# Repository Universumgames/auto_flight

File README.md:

# Auto Flight

Autonomous glider for area-coverage flights — technical documentation.

"Auto Flight" is an autonomous glider that independently flies over predefined areas (e.g. agricultural fields) in a lawn-mower (meander) pattern. Navigation is achieved through a combination of GPS, accelerometer/gyroscope (IMU), magnetometer, and barometer. Throughout the flight, the plane stays in contact with a ground station via a long-range radio link (LoRa), which provides a web interface for mission planning and live monitoring. In an emergency, the plane can be taken over manually at any time via an off-the-shelf RC transmitter.

The system consists of three independent firmware/software projects (the flight controller in the plane, the ground station, and a servo/motor controller) as well as a number of shared components and tools:

| Project | Platform | Task |
|---|---|---|
| [`flight_controller/`](./flight_controller) | ESP-IDF (ESP32-S3) | Main computer in the plane: route planning, sensors, flight control, LoRa communication |
| [`base_station/`](./base_station) | ESP-IDF (ESP32-S3) | Ground station: WiFi access point, web UI server, LoRa relay |
| [`motor_controller/`](./motor_controller) | PlatformIO/Arduino (ATmega328) | Control-surface/motor actuation, SBUS reception, safety override |
| [`frontend_web/`](./frontend_web) | Vue 3 + TypeScript | Ground station user interface (mission planning, live telemetry) |
| [`shared_components/`](./shared_components) | ESP-IDF components | Shared building blocks for flight controller and ground station (LoRa, I2C, sensor drivers, data storage) |

The project is an individual student project in the "Mobile Robots" module and is currently at the stage of an advanced prototype. An ongoing development log with progress and issues encountered can be found in [`resources/learning.md`](./resources/learning.md).

# Objective and application scenario

## Basic idea

The starting point of the project (see [`Projekt_Idee.md`](./Projekt_Idee.md)) is an autonomous glider that flies over defined areas. The version implemented as part of this work covers the beginning of this scenario: communication with the ground station, configuration, and monitoring of the flight. The plane is already able to compute a route from the given area and make small corrections during the flight based on the accelerometer. However, flying the route is not yet fully autonomous, since altitude control and thrust control have not yet been flight-tested.

## Application scenario

The system is designed for use in mapping and agriculture. With the addition of a camera, the system could be used to inspect large areas (e.g. agricultural fields, solar parks, forests). The ground station allows planning of the area to be flown over, monitoring of the flight, and evaluation of the sensor data. The system is intended for use in rural areas with low building density and no no-fly zones.

## Bandwidth and data-storage concept

Since LoRa only offers very low bandwidth at long range, the radio link is deliberately limited to compact status and control data (position, sensor values, routes, connection status). Larger payloads such as camera images are, in the original idea, intended for local storage (SD card) or WiFi transfer after landing, and are deliberately not part of the LoRa link. This part is not implemented in the current feature set, since no camera payload has been integrated.

# Requirements and constraints

## Functional requirements

- Autonomous navigation along a strip pattern (waypoint sequence) computed from a user-defined polygon
- Determination of position, attitude (roll/pitch), heading, and altitude during flight from GPS, IMU, magnetometer, and barometer
- Remote configuration of the target area and monitoring of the flight via a web interface, reachable through a WiFi access point provided by the ground station
- Telemetry transmission (position, key sensor data, connection status, route) over a long-range radio link between plane and ground station
- Manual override of control surfaces and propulsion at any time via an RC transmitter, independent of the state of the flight controller

## Non-functional requirements and constraints

- **Range vs. bandwidth:** The radio link must work reliably even over larger distances (field size). This requires choosing LoRa (868 MHz, ISM band), with correspondingly low usable data rate, which necessitates a custom, frugal message protocol (see section "Technical implementation").
- **Real-time capability:** Flight control runs with a fixed cycle time of 50 ms in order to respond promptly to changes in attitude and heading.
- **Resource constraints:** As a glider, weight is a limiting factor for battery capacity, sensors, and servos. This limits both the available compute power (microcontroller instead of single-board computer) and the number of I2C sensors that can be operated simultaneously on a shared bus.
- **Fail-safety:** Manual override must not depend on the state of the flight controller, since the flight controller itself is the actual failure source it is meant to guard against.
- **Legal framework:** During the project, research into the legal framework for autonomous aircraft was carried out (see week 2 in [`resources/learning.md`](./resources/learning.md)), which in particular confirmed the need for manual control to be available at all times.

## Technical constraints

- Two identical Heltec WiFi LoRa 32 V3 boards (ESP32-S3 + integrated SX1262 LoRa module) as the central compute and radio units, one in the plane and one in the ground station
- An Arduino Nano (ATmega328) as a separate, simple servo/motor controller, connected via I2C to the flight controller and via SBUS to the RC receiver
- ESP-IDF (version 5.x) as the firmware base for the flight controller and ground station, with shared components in [`shared_components/`](./shared_components)
- Node.js/Vue 3 for the web interface, which is embedded as static files into the ground station's flash storage (no separate web server)

# System architecture

## Hardware architecture

### Main components

| Component | Location | Function |
|---|---|---|
| Heltec WiFi LoRa 32 V3 (ESP32-S3 + SX1262) | Plane, ground station (2×) | Main computer + LoRa radio module |
| Arduino Nano (ATmega328) | Plane | Servo/motor actuation, SBUS reception, safety override |
| GPS module (ATGM336H, NMEA) | Plane (ground station optional) | Position determination |
| MPU6050 (accelerometer + gyroscope) | Plane | Attitude determination (roll/pitch) |
| Magnetometer HMC5883L | Plane | Heading determination |
| Barometer (BME280) | Plane, ground station | Altitude determination via air pressure |
| Level shifter (3.3 V <-> 5 V) | Plane | I2C level adaptation between ESP32-S3 (3.3 V) and Arduino Nano (5 V) |
| Time-of-flight sensor TOF200C | Plane | Ground-distance measurement, intended for automatic landing |
| SBUS receiver | Plane | Reception of RC transmitter commands |
| 4× servo / ESC | Plane | Ailerons (differential), elevator, thrust, rudder |
| LittleFS storage | Ground station | Storage of the web UI files in flash |
| Batteries | Plane, ground station | Power supply |

The complete bill of materials can be found in [`BOM.md`](./BOM.md). The TOF200C distance sensor is part of the procurement list, but is not yet integrated into the firmware in the current feature set, since automatic landing, as described in the section "Known limitations and possible improvements", has not yet been implemented.

The magnetometer originally used was a QMC5883P, which was replaced with an HMC5883L during the project. Both associated datasheets are available under [`resources/`](./resources); the reason for the switch is explained in the section "Technical implementation and key design decisions".

### Schematics

The schematics for the plane and ground station were originally created with [Fritzing](https://fritzing.org/). The source files are available as [`hardware/circuits/fritzing_source/schematics_plane.fzz`](./hardware/circuits/fritzing_source/schematics_plane.fzz) and [`hardware/circuits/fritzing_source/schematics_base.fzz`](./hardware/circuits/fritzing_source/schematics_base.fzz), together with custom Fritzing parts created for modules without official Fritzing support ([BMP280 breakout](./hardware/circuits/fritzing_source/BMP280_Breakout_Board.fzpz), [GT-U8 GPS module](./hardware/circuits/fritzing_source/GT-U8-GPS-module.fzpz), [Heltec WiFi Kit 32 (V3)](./hardware/circuits/fritzing_source/Heltec%20WiFi%20Kit%2032%20(V3).fzpz)).

Since Fritzing is no longer maintained, the design was also converted into KiCad projects: [`hardware/circuits/plane_pcb/`](./hardware/circuits/plane_pcb/) and [`hardware/circuits/base_station_pcb/`](./hardware/circuits/base_station_pcb/), covering both schematic capture and PCB footprint placement. There's no reliable automated Fritzing→KiCad converter, so this used a custom extraction pipeline (documented in [`hardware/circuits/tools/README.md`](./hardware/circuits/tools/README.md)) that rebuilds the netlist from the Fritzing source and generates the KiCad files from it. A few things to know before treating the KiCad projects as finished: symbols are placed on a plain auto-generated grid rather than a hand-arranged layout (both schematic and PCB), the PCB has no copper routing yet (only correct net assignments/ratsnest), and several breakout-board footprints use generic pin headers with dimensions noted as estimated where not confirmed from a datasheet — see the tooling README's "Known limitations" section for the full list before ordering boards.

The wiring of the 4 servos is not shown in the schematic here, in order to keep it clear. The servos are connected directly to the Arduino Nano, which generates the PWM signals. PWM pins 9, 10, 11, and 12 were used for the left aileron, right aileron, elevator, and rudder. The mapping between servo and control surface is defined in the control logic in the ESP32 flight controller and can be adjusted as needed. In the Arduino code there is a fixed mapping: byte 0 -> servo 1, byte 1 -> servo 2, byte 2 -> servo 3, byte 3 -> servo 4. Which servo is assigned to which control surface is then defined in the flight control logic in the ESP32 flight controller.

**Plane:**

**Ground station:**

### Mechanical design

Under [`3d_models/`](./3d_models) are the 3D-printed enclosure/mounting designs:

- **Ground station enclosure** ([`base_station_case.scad`](./3d_models/base_station_case.scad)): a two-piece enclosure (tray + lid) with a snap-fit connection, mounts for the main board (Heltec LoRa32 V3 + GPS module) and a daughterboard connected via cable (barometer), an SMA antenna feedthrough in the enclosure wall, and a pressure-equalization hole in the lid above the barometer.
- **Plane mounting plate** ([`plane_mount_plate.scad`](./3d_models/plane_mount_plate.scad)): according to a comment in the source code, a pure layout mockup showing the relative arrangement of the main board, two daughterboards, and the four control-surface servos. It is explicitly not a flight-worthy part (no fuselage mounting, no cable routing, no weight optimization).

### System topology

The control surfaces can be actuated via the servos either by the flight controller (over I2C) or directly by the RC transmitter (over SBUS). Which path is active is decided exclusively by the Arduino in the plane (see "Manual override").

## Software architecture

### Project structure

| Path | Content |
|---|---|
| [`flight_controller/`](./flight_controller) | ESP-IDF firmware of the plane: route planning, sensors, flight control, LoRa communication |
| [`base_station/`](./base_station) | ESP-IDF firmware of the ground station: WiFi AP, web UI server, LoRa relay |
| [`motor_controller/`](./motor_controller) | Arduino firmware for servo/SBUS integration |
| [`frontend_web/`](./frontend_web) | Vue 3 web interface of the ground station |
| [`shared_components/`](./shared_components) | ESP-IDF components shared between flight controller and ground station (LoRa, I2C, sensor drivers, data storage) |
| [`python/`](./python) | Offline visualization of the computed flight routes |
| [`serial_plane_viz/`](./serial_plane_viz) | Tool for visualizing servo deflections over the serial interface |
| [`doc/`](./doc), [`resources/`](./resources) | Notes, pinouts, datasheets, bill of materials, development log |

`flight_controller` and `base_station` are two independent ESP-IDF projects, each with its own `sdkconfig`/`CMakeLists.txt`, both of which include the same components from `shared_components/` via `EXTRA_COMPONENT_DIRS`. This is the project's central reuse strategy: sensor drivers, I2C management, the LoRa radio stack, and the application protocol exist only once and are shared by both firmware projects, controlled via a project-wide compile flag (`FLIGHT_DEVICE_TYPE_PLANE` or `FLIGHT_DEVICE_TYPE_BASE_STATION`), which determines which role a device takes on in the protocol.
`motor_controller` is a standalone Arduino project that communicates with the flight controller over I2C and drives the control-surface servos and the motor. It is deliberately kept simple, since its only task is to move the servos and receive the SBUS signals from the transmitter.

### Communication layers

The connection between plane and ground station is split into three layers:

1. **Radio layer** ([`shared_components/lora_com`](./shared_components/lora_com)): controls the SX1262 radio module via the RadioLib library. Since a LoRa packet is limited to 255 bytes, this layer implements its own fragmentation of larger messages (header with message ID, fragment ID, and total fragment count), acknowledgement of each fragment via ACK with a timeout (2 s) and up to three retries, as well as periodic keep-alive pings (default: every 30 s) to monitor the connection in case no other message is sent.
2. **Application protocol** ([`shared_components/flight_com`](./shared_components/flight_com)): defines typed packets on top of the radio layer, including `SensorUpdate` (air pressure, heading), `PositionUpdate` (GPS position), `ComponentStatus` (connection status of the individual subsystems, override status, flight state), `PlannedRoutePacket`/`PlannedAreaPacket` (computed route / given area), and `FlightHistoryPacket` (flown path).
3. **Web link** (ground station -> browser): the ground station does not directly forward the received LoRa packets, but instead writes them into a central, thread-safe state store (`FlightStorage`, part of [`shared_components/flight_data`](./shared_components/flight_data)). An HTTP/WebSocket server reads from it and serializes the data separately as JSON for the web frontend. The LoRa format and the web JSON format are thus fully decoupled.

### Ground station web stack

The ground station opens a WiFi AP (default SSID, configurable via Kconfig, alternatively a "dev mode" in which it first tries to connect to an existing WiFi network instead) as well as an HTTP server. This serves:

- **Static files** of the web interface from a LittleFS flash partition (`/*` route as a fallback handler). The directory `base_station/static` is a symlink to `frontend_web/dist`, so that a frontend build is directly embedded as a flash image (`littlefs_create_partition_image` in [`base_station/CMakeLists.txt`](./base_station/CMakeLists.txt)).
- **REST API endpoints**: including `GET /api/status` (connection status), `POST`/`GET /api/area` (set/read target area), `GET /api/route` (query computed route). See "Ground station API reference" below for details.
- **WebSocket endpoint** (`GET /api/ws`): sends three message types to all connected clients every 5 seconds: `flight` (positions, planned/flown route), `connection` (connection status of all subsystems), `sensor` (air pressure, computed altitude, heading). Details below.

### Ground station API reference

All HTTP and WebSocket endpoints are registered in the ESP-IDF component [`base_station/components/frontend`](./base_station/components/frontend) (`FrontendHandlerClass::init()`), not in `base_controller`. At startup, `httpd_start` is called first, then the LittleFS partition is mounted, and finally the handlers are registered in a fixed order: `/api/ping`, `/api/ws`, the remaining REST endpoints, and finally the static file handler `/*`. This order is necessary because `/*`, as a wildcard, would otherwise shadow all more specific routes. In parallel, a FreeRTOS task starts that sends status packets via WebSocket every 5 seconds.

#### Data types

All endpoints exchange JSON, which is (de)serialized directly from the C++ structs in [`FrontendPackets.hpp`](./base_station/components/frontend/FrontendPackets.hpp) via `nlohmann::json`. The types in the frontend ([`frontend_web/src/types/`](./frontend_web/src/types)) mirror the same structures in TypeScript:

```ts
type Coordinate = { longitude: number; latitude: number }
type Route = Coordinate[]

type ConnectionState = "connecting" | "connected"
type FlightState = "planning" | "planned" | "flying" | "returning"

interface AreaDefinePacket {
  shape: Coordinate[]
}

interface PlannedRoutePacket {
  type: "plannedRoute"
  route: Coordinate[]
}

interface ConnectionUpdatePacket {
  type: "connection"
  baseConnectionState: ConnectionState
  lastContactBaseStationTimestamp: number
  planeConnectionState: ConnectionState
  lastContactPlaneTimestamp: number
  gpsConnectionBase: ConnectionState
  gpsConnectionPlane: ConnectionState
  barometerConnectionBase: ConnectionState
  barometerConnectionPlane: ConnectionState
  motorComConnectionPlane: ConnectionState
  magnetometerConnectionPlane: ConnectionState
  accelerometerConnectionPlane: ConnectionState
  manualOverridePlane: boolean
  flightState: FlightState
}

interface FlightUpdatePacket {
  type: "flight"
  basePosition: Coordinate
  basePositionUpdateTime: number
  planePosition: Coordinate
  planePositionUpdateTime: number
  flightRoute: Route
  flightRouteUpdateTime: number
  plannedRoute: Route
  plannedRouteUpdateTime: number
}

interface SensorUpdatePacket {
  type: "sensor"
  barometerPressureBase: number
  barometerPressurePlane: number
  calculatedAltitude: number
  headingPlane: number
}
```

`...Timestamp`/`...UpdateTime` fields are Unix timestamps, originating either from runtime or from the GPS signal. `ConnectionState`/`FlightState` are serialized as strings rather than numbers.

#### Endpoints

| Method | Path | Function | Type |
|---|---|---|---|
| GET | `/api/ping` | Liveness check | Text `"pong"` |
| GET | `/api/ws` | WebSocket upgrade, live telemetry | see below |
| GET | `/api/status` | Connection and flight state | `ConnectionUpdatePacket` |
| POST | `/api/area` | Set target area | Body: `AreaDefinePacket` |
| GET | `/api/area` | Query target area | `AreaDefinePacket` |
| GET | `/api/route` | Query computed route | `PlannedRoutePacket` |
| GET | `/*` | Static web UI files from LittleFS | — |

**WebSocket `/api/ws`**
After the upgrade, the client is registered and supplied with three messages every 5 seconds, distinguished by `type`: `FlightUpdatePacket`, `ConnectionUpdatePacket`, `SensorUpdatePacket` (type definitions above). If a client sends the text message `"ping"`, the server responds with `"pong"` (used in the frontend as a connection heartbeat). The type of the WebSocket message is currently distinguished via the first field `type` in the JSON object, not via WebSocket subprotocol mechanisms.

### Frontend

The web interface ([`frontend_web/`](./frontend_web)) is a Vue 3/TypeScript single-page application built with Vite. It guides the operator through mission preparation via a wizard:

- **Connection overview**: shows the live status of the base and plane connections as well as their subsystems (GPS, barometer, motor actuation, magnetometer), and only unlocks the next step once all connections are established.
- **Area planning**: drawing a target polygon on a Leaflet map (via `leaflet-draw`), transmitted to the ground station.
- **Route preview**: querying the route computed by the plane, displayed on the map together with the path flown so far.
- **Live telemetry**: continuous updates of position, route, and sensor values via the WebSocket connection, supplemented by a dedicated ping/pong heartbeat in the frontend to detect connection drops.

# Technical implementation and key design decisions

## Route planning

The [`route_planner`](./flight_controller/components/route_planner) generates a lawn-mower/boustrophedon pattern from a polygon drawn by the operator:

1. **Generate sweep lines**: equidistant, horizontal lines (parallel to latitude) are computed from the polygon's bounding box, spaced by the effective swath width.
2. **Clip to the polygon**: each line is intersected with the actual, possibly concave, polygon (geometry library [`homog2d`](https://github.com/skramm/homog2d)). Where multiple intersection points occur, only the outer segment is kept, so that holes and concave shapes are correctly excluded.
3. **Assemble the path**: the individual lines are alternately connected left-to-right and right-to-left into a continuous path. Additional intermediate points are inserted between two rows to produce a softer curved path instead of a sharp 180° turn.
4. **Interpolation**: finally, all segments longer than a configured maximum distance are subdivided into evenly spaced intermediate points, so that two consecutive waypoints are never further apart than this distance. This interpolation should later be usable for camera control and is not only relevant for flight control.

In the current implementation, the flight controller calls the route planner with a maximum point distance of 60 m, a swath width of 40 m, and an overlap factor of 20%, which corresponds to an effective row spacing of 32 m. These values are currently hardcoded in the source code and not configurable. For the later integration of a camera, this would be related to the camera's effective image width/FOV, the flight altitude, and a desired additional overlap between images, in order to determine the parameters for route planning.

## Flight control

The flight controller ([`FlightController`](./flight_controller/components/flight_controller)) runs as a FreeRTOS task with a fixed cycle of 50 ms and implements cascaded PI control for four control quantities:

- **Rudder (heading):** the target bearing is computed from the current GPS position and the next waypoint and compared with the measured compass heading. The normalized bearing error is mapped proportionally (P control) to the rudder.
- **Altitude hold:** the difference between target altitude (60 m) and measured altitude drives two parallel PI controllers: one for thrust and one for the target pitch angle, which in turn feeds into the pitch control as a setpoint (cascaded control).
- **Ailerons:** pure "wings-level" control (PI on roll angle), independent of any turn command. There is currently no coordinated turn; turning is done exclusively via the rudder.
- **Elevator:** PI control of the pitch angle towards the target pitch given by the altitude control.

Waypoint arrival is checked via the distance to the current position against a configurable radius (default 30 m). Once the last waypoint is reached, the internal flight state switches to "returning". In the current implementation, however, this has no effect yet. Unlike, for example, the telemetry interval or waypoint radius, controller gains and target altitude are hardcoded as constants in the source code rather than being Kconfig parameters.

## Sensors and data fusion

Sensor data processing is deliberately kept simple: there is **no** shared state estimator in use. Instead, each derived measurement is independently smoothed with a moving average and fed directly into the respective PI controller:

- **Attitude (roll/pitch):** computed exclusively from the direction of gravity from the accelerometer (`atan2` over the acceleration components), after a zero-point calibration at startup.
- **Heading:** computed directly from the raw magnetometer values (`atan2`), without tilt compensation relative to roll/pitch and without correction for magnetic declination. The value is then smoothed circularly (separate averaging of sine/cosine components, to correctly handle the jump at 0°/360°).
- **Altitude:** from barometric air pressure via the hydrostatic equation, relative to a ground reference pressure transmitted by the ground station. The computed altitude is thus relative to the starting point (AGL), not absolute (MSL).
- **Position:** directly from parsed GPS NMEA sentences, without additional filtering or dead reckoning. A position is only considered valid once a minimum number of satellites has been received.

This architecture should be understood as a pragmatic intermediate stage. It delivers usable, but more vibration- and noise-sensitive estimates than true sensor fusion (see "Known limitations").

## Communication between flight controller and motor controller

The Arduino motor controller is an I2C slave (address `0x42`) with a deliberately minimal, register-less protocol:

- **Write (flight controller → Arduino):** exactly 4 bytes, one signed value each in the range -100…100 for rudder, elevator, thrust, and differential aileron. Incomplete transfers are discarded. The last valid values are retained.
- **Read (Arduino → flight controller):** a single status byte indicating whether manual override is active. A successful read also serves as a connection check.

The Arduino independently monitors the freshness of incoming I2C messages and automatically reinitializes the I2C bus if no message has arrived for one second. This is a safeguard against stuck bus states, which were observed multiple times during the project.

## Manual override

The safety-critical decision of whether the plane is controlled autonomously or manually is deliberately not made in the flight controller, but on the Arduino. A fixed SBUS channel (channel 5) of the RC receiver is interpreted as an override switch. If its value exceeds the threshold of 1500 µs (neutral position), the Arduino drives the four servos directly from the SBUS channels and ignores the I2C values last received from the flight controller. The flight controller itself only reads the override status for display/telemetry purposes, but has no influence on it. This decoupling ensures that manual control is preserved even in the event of a crash or hang of the ESP32 firmware.
The current setup uses the MRFS01 SBUS receiver from Futaba (link to [Aliexpress](https://de.aliexpress.com/item/1005007253167246.html)). The SBUS receiver transmits the control commands to the Arduino over a serial interface (UART), but Futaba uses a special configuration of the UART interface. The Arduino library [SBUS](https://github.com/george-hawkins/arduino-sbus) supports this configuration, with a few hardware modifications for the Arduino Nano.
The Futaba SBUS receiver communicates over an inverted UART interface at 100000 baud, 8 data bits, 2 stop bits, and even parity. The Arduino Nano, however, does not have an inverted UART interface, so an inversion of the UART signals was implemented using a 2N2222 transistor. The circuit can be found in the schematic file [`hardware/circuits/fritzing_source/schematics_plane.fzz`](./hardware/circuits/fritzing_source/schematics_plane.fzz) (also viewable as symbol `U1` in the KiCad schematic, see the section [Schematics](#schematics)).

## Key design decisions during the project

- **Switch from PlatformIO to ESP-IDF** for the flight controller and ground station (week 4 of the development log): triggered by difficulties in component management under PlatformIO. ESP-IDF also made it possible to build and test the same components natively on the host machine (see "Tests and evaluation").
- **Switch of the magnetometer from QMC5883P to HMC5883L**, along with switching the read mode from "continuous" to "single-read" (weeks 10 and 11): the originally installed QMC5883P responded unreliably and sometimes under changing I2C addresses. The deeper cause of a recurring bus failure was identified later: in continuous measurement mode, a read access during an ongoing internal measurement can put the sensor into a state that blocks the entire I2C bus or fills it with garbage data, instead of just returning a single faulty reading. Switching to individually requested measurements (single-read) fixes this behavior, since the sensor only allows read accesses after a measurement has completed.
- **Custom fragmentation protocol over LoRa**: since individual application messages (e.g. a complete planned route) can exceed the maximum LoRa packet size of 255 bytes, a custom fragmentation and acknowledgement scheme with message/fragment IDs, inspired by TCP, was developed.
- **Separation of radio protocol and web protocol**: the deliberate decoupling of the LoRa wire format and the WebSocket/REST JSON format via the central `FlightStorage` state store allows both sides to be developed further independently of each other.

## Supporting tools

Two tools support development but are not part of the actual flight software:

- [`python/`](./python): two small scripts for offline visualization of the sweep paths generated by the route planner, either as a simple 2D plot (`matplotlib`) or on an interactive map (`folium`).
- [`serial_plane_viz/`](./serial_plane_viz): a browser tool (three.js) that visualizes servo deflections (motor, roll, pitch, yaw), sent over a serial interface in the same value range as the motor controller's I2C protocol, on a simple 3D plane model. This is useful for debugging without a real plane.

# Tests and evaluation

## Automated tests

**Flight controller (native unit tests):** the `flight_controller` build system distinguishes between a real ESP-IDF firmware build and a native host build based on an environment variable. For the latter, a dedicated CMake compatibility layer exists that makes ESP-IDF components compilable as ordinary CMake libraries for the host, so that the business logic can be tested without real hardware (GoogleTest). In terms of content, the existing tests are limited exclusively to the **geometry of route planning**: correct detection of the outer polygon points, correct intersection computation between a line and the polygon, correct number/position of the generated sweep lines, and a monotonic course of the assembled sweep path. There are **no** automated tests for flight control (PI controllers), the sensor drivers, or the I2C protocol to the motor controller. This part is verified exclusively on real hardware.

**Frontend:** type checking (`vue-tsc`) and linting (ESLint/oxlint) run as basic quality assurance on every build. A Playwright E2E scaffold is set up. However, the only existing test is the unchanged scaffold test from the Vue project template; real tests covering actual functionality have not yet been implemented, due to the application's continuous changes and extensions.

## Evaluation based on the development history

The development log ([`resources/learning.md`](./resources/learning.md)) documents progress over twelve weeks and allows an honest assessment of the functionality actually achieved:

- Successfully implemented and put into operation: GPS evaluation, a working LoRa connection with acknowledgements and keep-alive pings, the I2C connection of barometer and IMU, and, after the hardware problems described above, a working magnetometer connection.
- Several fundamental technical problems had to be solved during development, including a necessary packet fragmentation for LoRa messages over 255 bytes, a deadlock in the event handler queue, and the I2C bus dropouts related to the magnetometer described above.
- Recurring I2C bus instability when operating multiple sensors on the same bus simultaneously was the longest-standing hardware/firmware problem during the project and, even with the implemented workarounds (bus recovery, single-read mode), should still be regarded as a fundamental residual risk.

# Known limitations and possible improvements

**Sensor fusion:** attitude determination is done purely from the accelerometer; a Kalman or complementary filter is not active, and the compass operates without tilt compensation or declination correction. As an improvement, the existing complementary filter and gyroscope integration should actually be incorporated into the control loop, and tilt compensation and declination should be added to the heading calculation.

**Control:** controller gains and target altitude are hardcoded instead of configurable, there is no coordinated turn (ailerons independent of the turn command), and the full control cascade has not been flight-tested. This could be improved by making the gains configurable via Kconfig or at runtime, carrying out systematic flight tests, and adding coordinated turn control.

**Mission parameters & configurability:** swath width, overlap factor, and maximum point distance are hardcoded in the source code for route planning (see the "Route planning" section) and not configurable, in order to tune them to different cameras (FOV, model), battery capacities, or plane sizes/weights; likewise, there is no configuration at all for coordinated operation of multiple planes (swarm configuration). It would make sense to make these mission parameters configurable via the web interface and to extend the communication/addressing layer (see "Radio link") so that multiple planes and base stations can be coordinated as a swarm.

**Path-planning algorithms:** currently only a sweep-line lawn-mower pattern is implemented; alternative coverage-path-planning algorithms have not been tried out or evaluated. A systematic evaluation of different algorithms in terms of flight distance, theoretical flight duration, and estimated battery capacity is still outstanding and would be a sensible next step to make route planning energy- and runtime-aware beyond pure geometry.

**Hardware robustness:** with multiple sensors connected, recurring I2C bus dropouts occur, which remain a residual risk despite workarounds. As an improvement, it would make sense to reconsider the bus topology (e.g. I2C multiplexer, separate buses) and carry out a hardware redesign of the wiring.

**Radio link:** no encryption is active, there is no device addressing (only point-to-point, relevant for multiple planes/base stations), and airtime is not controlled. There is potential for improvement in enabling encryption, adding addressing for multi-plane scenarios, and implementing control of maximum airtime.

**Test coverage:** only the route-planning geometry is automatically tested, the CI only builds the documentation and not the firmware or the frontend, and the frontend E2E test is unchanged scaffold code. Unit tests for control logic and protocol code should be added here, firmware/frontend build and tests should be added to the CI pipeline, and the Playwright test should be adapted to the real application.

**Frontend code:** the frontend is not yet finished. Still missing are further options for configuring the flight-route computation, flight monitoring once the flight has started, and a return-to-home function. There is also currently a problem loading the tiles for the OpenStreetMap map. Since the end device is on the base station's WiFi network, which does not offer internet access, the map view currently only works if a separate hotspot is opened or if one switches temporarily to mobile data to load the map. A SIM module would be a solution to this problem. Alternatively, switching to a native app communicating via Bluetooth would be an elegant option, as it would make it possible to use the phone's offline maps.

**Flight tests:** no real flight tests have been carried out, since altitude control and thrust control are not yet adequately implemented; in addition, the existing servo controls still need to be verified. As a next step, systematic flight tests should be carried out, possibly with a safety tether or in a cordoned-off test area.

**Camera integration:** the camera has so far been left out of this prototype. Image coverage is in principle computable from FOV and ground distance, but a reliable ground-distance measurement is still missing: the barometer and GPS only provide altitude above the starting point/sea level and fail in hilly or mountainous terrain without an accompanying elevation map; a LiDAR sensor for ranges beyond 40 m would also still need to be added. For image processing, there is the idea of fire/smoke detection. For this, one could try to run a small quantized CNN on an ESP (inspired by the project [ESP32 LLM](https://github.com/DaveBben/esp32-llm)). As a naive, more resource-efficient alternative, a simple heuristic algorithm could be used instead (e.g. gray/red proportion in the image, optionally supported by a thermal camera). Next steps would be connecting a real camera to this ESP32 prototype, integrating it into the overall process (flight controller/ground station), and a comparative test of both approaches (naive vs. CNN) in terms of detection quality and resource usage.

# Individual contributions

The project was carried out as an individual work (one author according to the task assignment and version control). Conception, the entire firmware development (flight controller, ground station, motor controller), development of the web interface, selection and integration of the hardware, and this documentation all come entirely from the same person. A division among multiple contributors therefore does not apply.
AI tools were used to a small extent to assist with refactoring or the development of the 3D visualization. However, the essential parts of the software development, in particular the system design, system structure, and system logic, were implemented without AI.

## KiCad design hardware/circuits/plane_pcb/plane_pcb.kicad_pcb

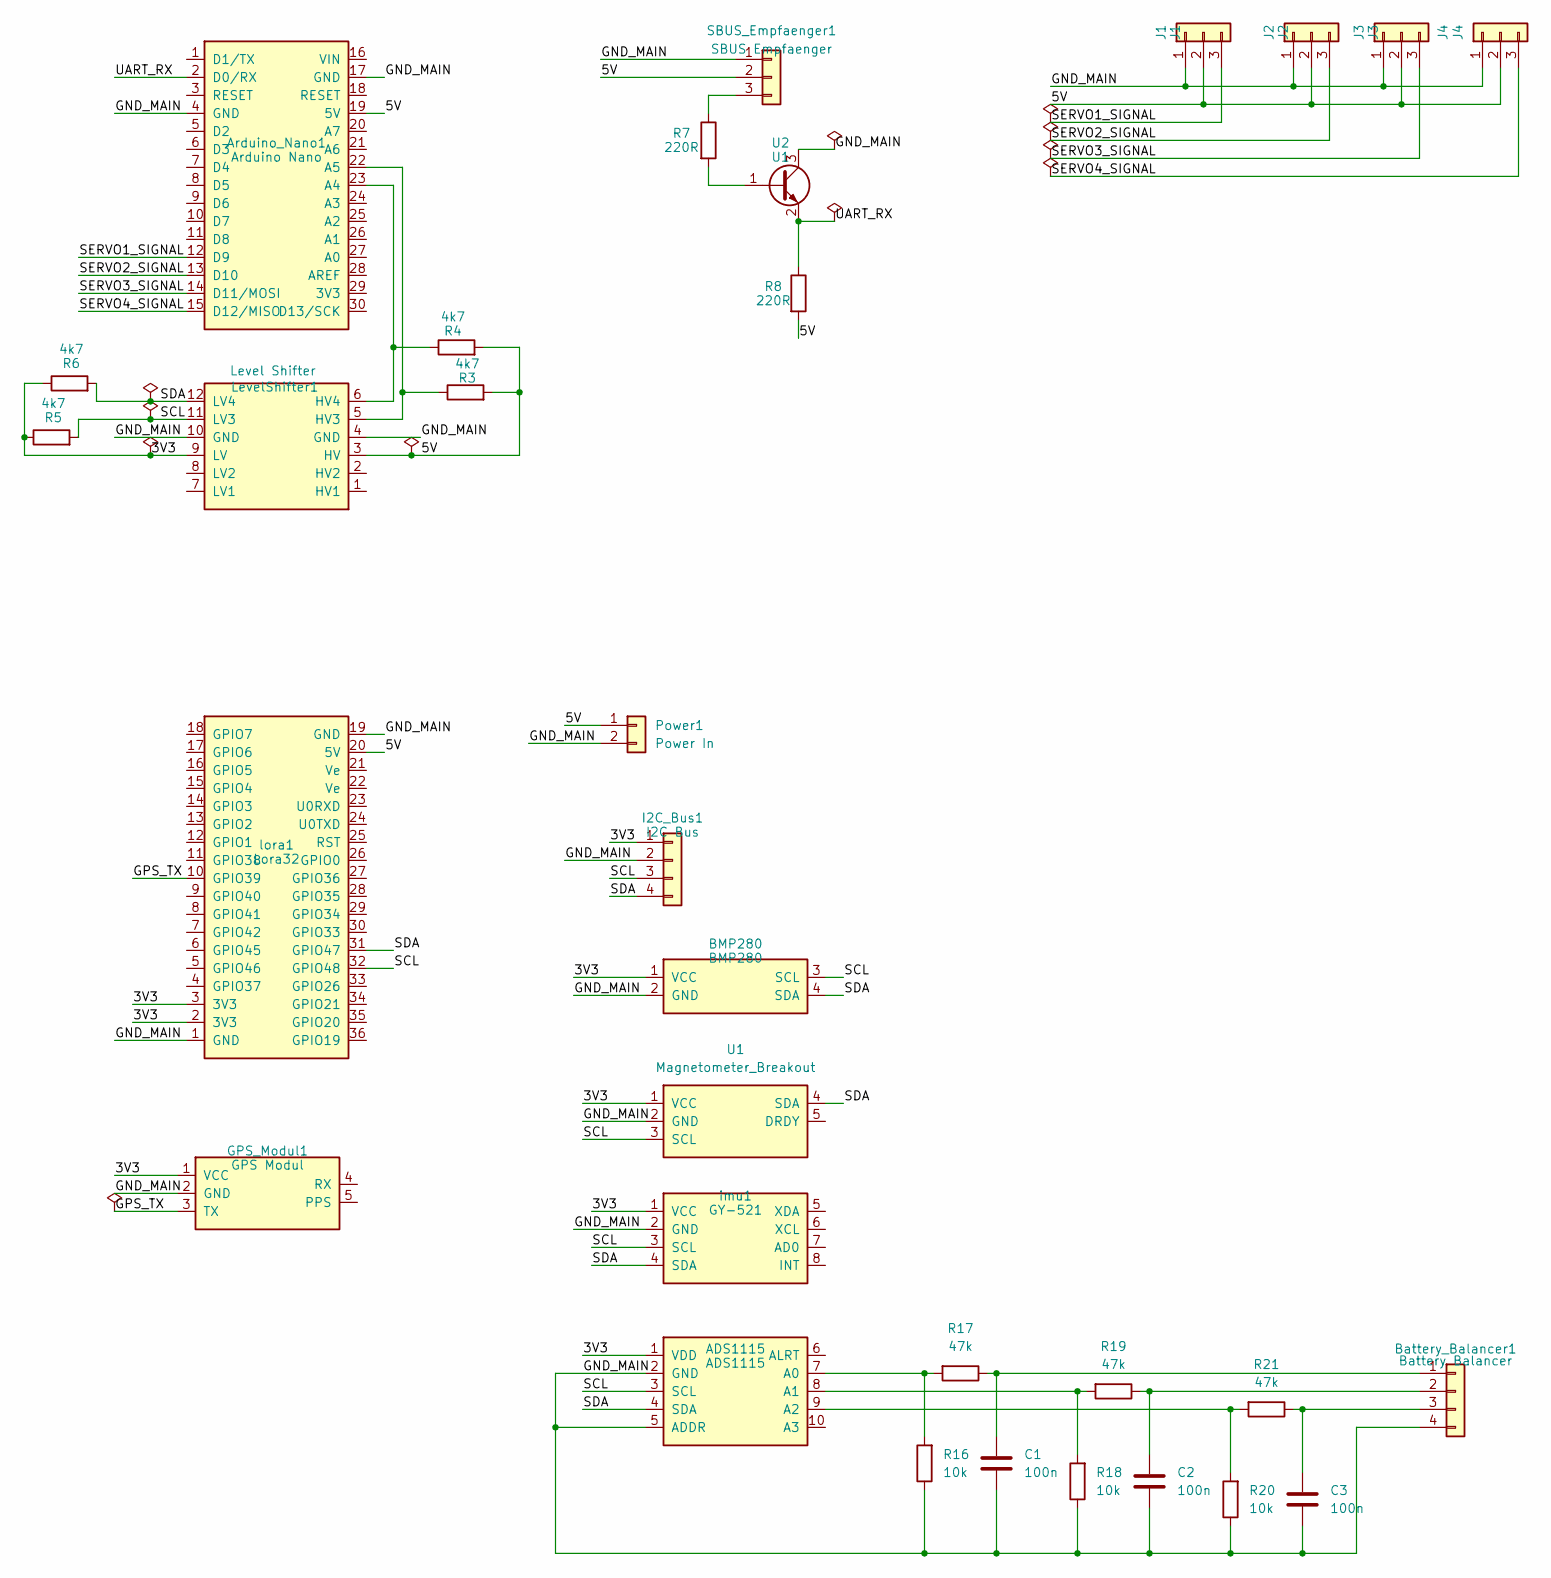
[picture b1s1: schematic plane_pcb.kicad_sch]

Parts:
ADS1115: ADS1115; PinHeader_1x10_P2.54mm_Vertical
Arduino_Nano1: Arduino Nano; Arduino_Nano
BMP280: BMP280; PinHeader_1x04_P2.54mm_Vertical
Battery_Balancer1: Battery Balancer; JST_EH_B4B-EH-A_1x04_P2.50mm_Vertical
C1, C2, C3: 100n; C_1206_3216Metric_Pad1.33x1.80mm_HandSolder
GPS_Modul1: GPS Modul; PinHeader_1x05_P2.54mm_Vertical
I2C_Bus1: I2C Bus; JST_EH_B4B-EH-A_1x04_P2.50mm_Vertical
J1: J1; PinHeader_1x03_P2.54mm_Vertical
J2: J2; PinHeader_1x03_P2.54mm_Vertical
J3: J3; PinHeader_1x03_P2.54mm_Vertical
J4: J4; PinHeader_1x03_P2.54mm_Vertical
LevelShifter1: Level Shifter; I2C_Level_Converter
Power1: Power In; JST_EH_B2B-EH-A_1x02_P2.50mm_Vertical
R3, R4, R5, R6: 4k7; R_1206_3216Metric_Pad1.30x1.75mm_HandSolder
R7, R8: 220R; R_1206_3216Metric_Pad1.30x1.75mm_HandSolder
R16, R18, R20: 10k; R_1206_3216Metric_Pad1.30x1.75mm_HandSolder
R17, R19, R21: 47k; R_1206_3216Metric_Pad1.30x1.75mm_HandSolder
SBUS_Empfaenger1: SBUS Empfaenger; PinHeader_1x03_P2.54mm_Vertical
U1: Magnetometer_Breakout; PinHeader_1x05_P2.54mm_Vertical
U2: U1; TO-92_Inline
imu1: GY-521; PinHeader_1x08_P2.54mm_Vertical
lora1: Lora32; Heltec_WiFi_LoRa_32_V3.2

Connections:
/3V3: ADS1115.1 (VDD), BMP280.1 (VCC), GPS_Modul1.1 (VCC), I2C_Bus1.1, LevelShifter1.9 (LV), R5.1, R6.1, U1.1 (VCC), imu1.1 (VCC), lora1.2 (3V3), lora1.3 (3V3)
/5V: Arduino_Nano1.19 (5V), J1.2, J2.2, J3.2, J4.2, LevelShifter1.3 (HV), Power1.1, R3.2, R4.2, R8.2, SBUS_Empfaenger1.2, lora1.20 (5V)
/GND_MAIN: ADS1115.2 (GND), ADS1115.5 (ADDR), Arduino_Nano1.4 (GND), Arduino_Nano1.17 (GND), BMP280.2 (GND), Battery_Balancer1.4, C1.2, C2.2, C3.2, GPS_Modul1.2 (GND), I2C_Bus1.2, J1.1, J2.1, J3.1, J4.1, LevelShifter1.4 (GND), LevelShifter1.10 (GND), Power1.2, R16.1, R18.1, R20.1, SBUS_Empfaenger1.1, U1.2 (GND), U2.3 (C), imu1.2 (GND), lora1.1 (GND), lora1.19 (GND)
/GPS_TX: GPS_Modul1.3 (TX), lora1.10 (GPIO39)
/SCL: ADS1115.3 (SCL), BMP280.3 (SCL), I2C_Bus1.3, LevelShifter1.11 (LV3), R5.2, U1.3 (SCL), imu1.3 (SCL), lora1.32 (GPIO48)
/SDA: ADS1115.4 (SDA), BMP280.4 (SDA), I2C_Bus1.4, LevelShifter1.12 (LV4), R6.2, U1.4 (SDA), imu1.4 (SDA), lora1.31 (GPIO47)
/SERVO1_SIGNAL: Arduino_Nano1.12 (D9), J1.3
/SERVO2_SIGNAL: Arduino_Nano1.13 (D10), J2.3
/SERVO3_SIGNAL: Arduino_Nano1.14 (D11/MOSI), J3.3
/SERVO4_SIGNAL: Arduino_Nano1.15 (D12/MISO), J4.3
/UART_RX: Arduino_Nano1.2 (D0/RX), R8.1, U2.2 (E)
unnamed: ADS1115.7 (A0), R16.2, R17.2
unnamed: ADS1115.8 (A1), R18.2, R19.2
unnamed: ADS1115.9 (A2), R20.2, R21.2
unnamed: Arduino_Nano1.23 (A4), LevelShifter1.6 (HV4), R4.1
unnamed: Arduino_Nano1.22 (A5), LevelShifter1.5 (HV3), R3.1
unnamed: Battery_Balancer1.1, C1.1, R17.1
unnamed: Battery_Balancer1.2, C2.1, R19.1
unnamed: Battery_Balancer1.3, C3.1, R21.1
unnamed: R7.1, SBUS_Empfaenger1.3
unnamed: R7.2, U2.1 (B)

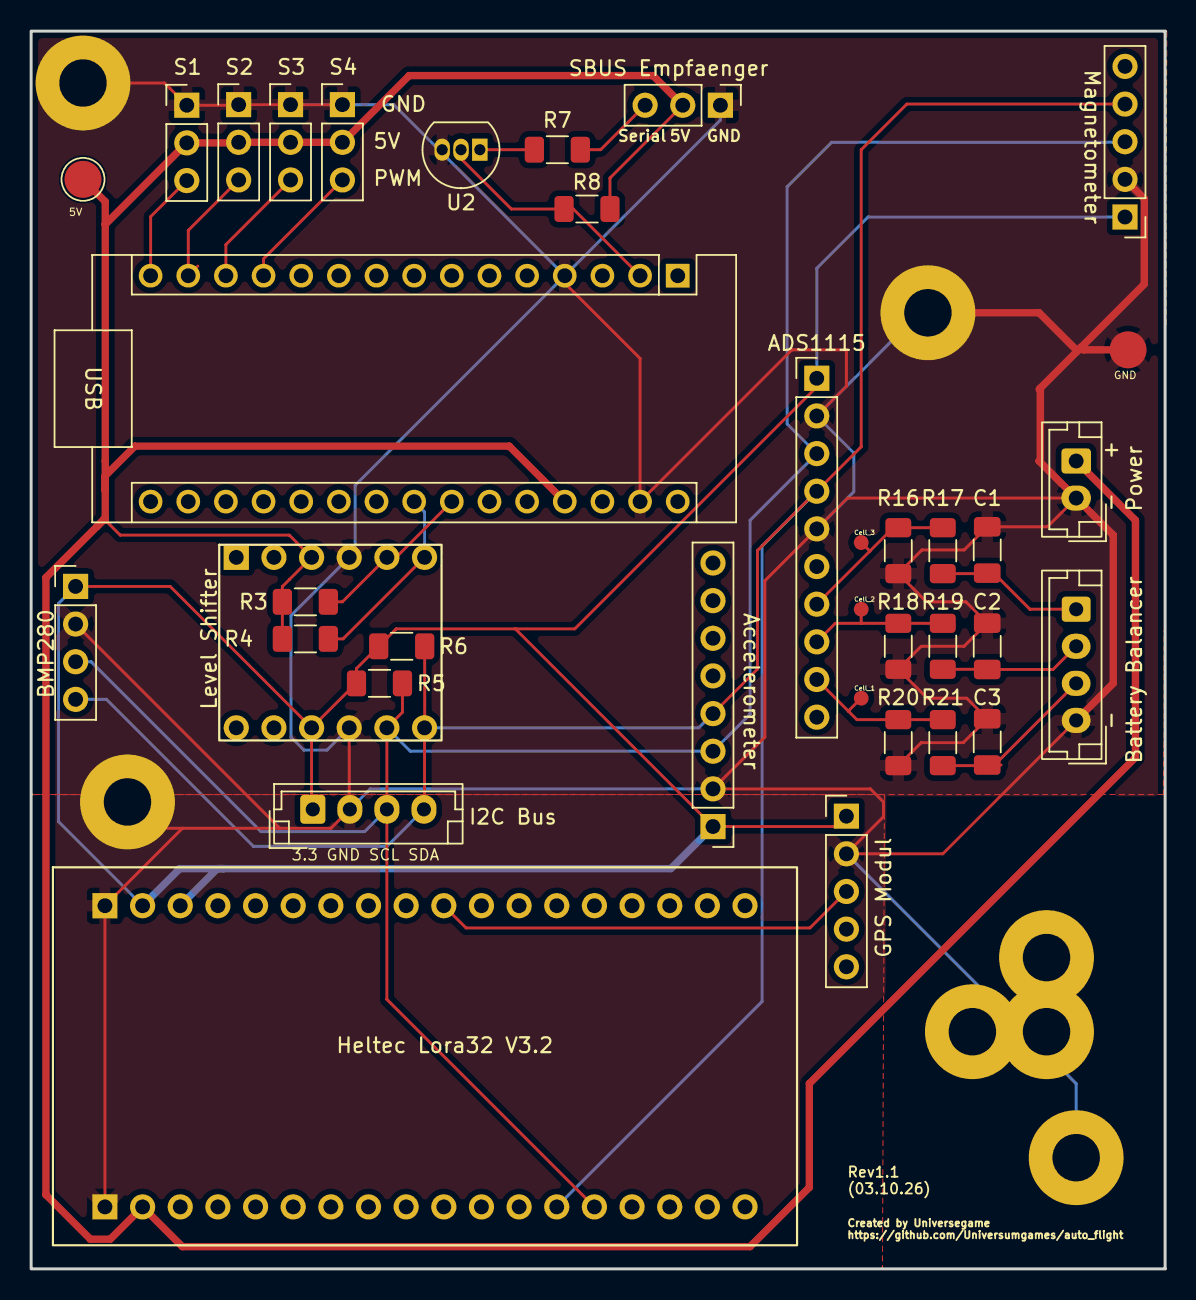
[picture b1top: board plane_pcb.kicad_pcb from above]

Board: 2 copper layers, 76.5 x 83.5 mm, 32 parts (0 on the bottom side), 21 nets.

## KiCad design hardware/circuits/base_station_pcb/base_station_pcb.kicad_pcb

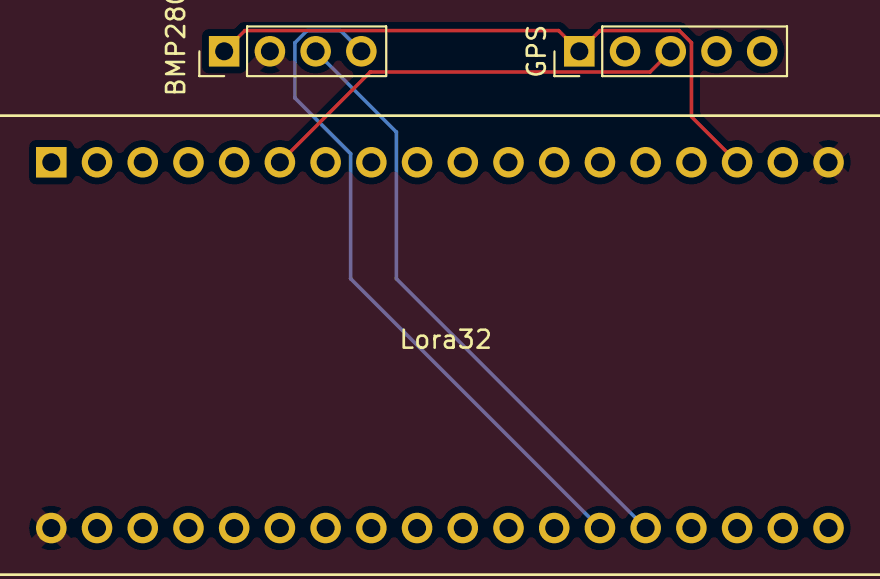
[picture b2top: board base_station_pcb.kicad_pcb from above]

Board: 2 copper layers, 3 parts (0 on the bottom side), 5 nets.

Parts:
BMP280: BMP280; PinHeader_1x04_P2.54mm_Vertical
GPS: GPS Module; PinHeader_1x05_P2.54mm_Vertical
Lora32: lora32; Heltec_WiFi_LoRa_32_V3.2

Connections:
/GND: BMP280.2 (GND), GPS.2 (GND), Lora32.18 (GND), Lora32.19 (GND)
/SCL: BMP280.3 (SCL), Lora32.32 (GPIO48)
/SDA: BMP280.4 (SDA), Lora32.31 (GPIO47)
/UART_RX: GPS.3 (TX), Lora32.6 (GPIO2)
/VCC: BMP280.1 (VCC), GPS.1 (VCC), Lora32.16 (3V3)

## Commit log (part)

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2026-04-11 init commit
2026-04-27 get gps to work and decoding, start with lora and route planning
2026-05-04 init
2026-05-06 first path planning draft
2026-05-06 switch flight controller from platformio to esp idf project
2026-05-07 switch base station to esp idf, fix compile and cleanup
2026-05-07 fix issues with esp idf 6.0
2026-05-07 fix unit tests with native runtime
2026-05-09 get web interface and wifi working for base station
2026-05-09 init web interface
2026-05-10 get minimal websocket with heartbeat working
2026-05-10 misc updates
2026-05-18 getting lora working
2026-05-22 get remote control switch/proxy working, prepare flight communication from esp to arduino
2026-06-02 update frontend to work with api endpoints
2026-06-02 update plane module to integrate components
2026-06-02 fix bugs and refactor
2026-06-04 fix lora communication bugs
2026-06-04 add sdk config
2026-06-05 fix serialization
2026-06-05 cleanup lora isr
2026-06-05 cleanup
2026-06-22 cleanup bugfixes, motor communication/servo fixes, integration fixes
2026-06-24 get magnetometer working
2026-06-28 bugfixes, adding magnetometer, and fix component statuses in webui
